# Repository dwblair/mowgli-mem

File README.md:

#mowgli-mem

https://github.com/adafruit/DS1307-breakout-board

https://tronixlabs.com.au/components/ics/real-time/microchip-rtc-mcp7940n-i-p-ds1307-equivalent/

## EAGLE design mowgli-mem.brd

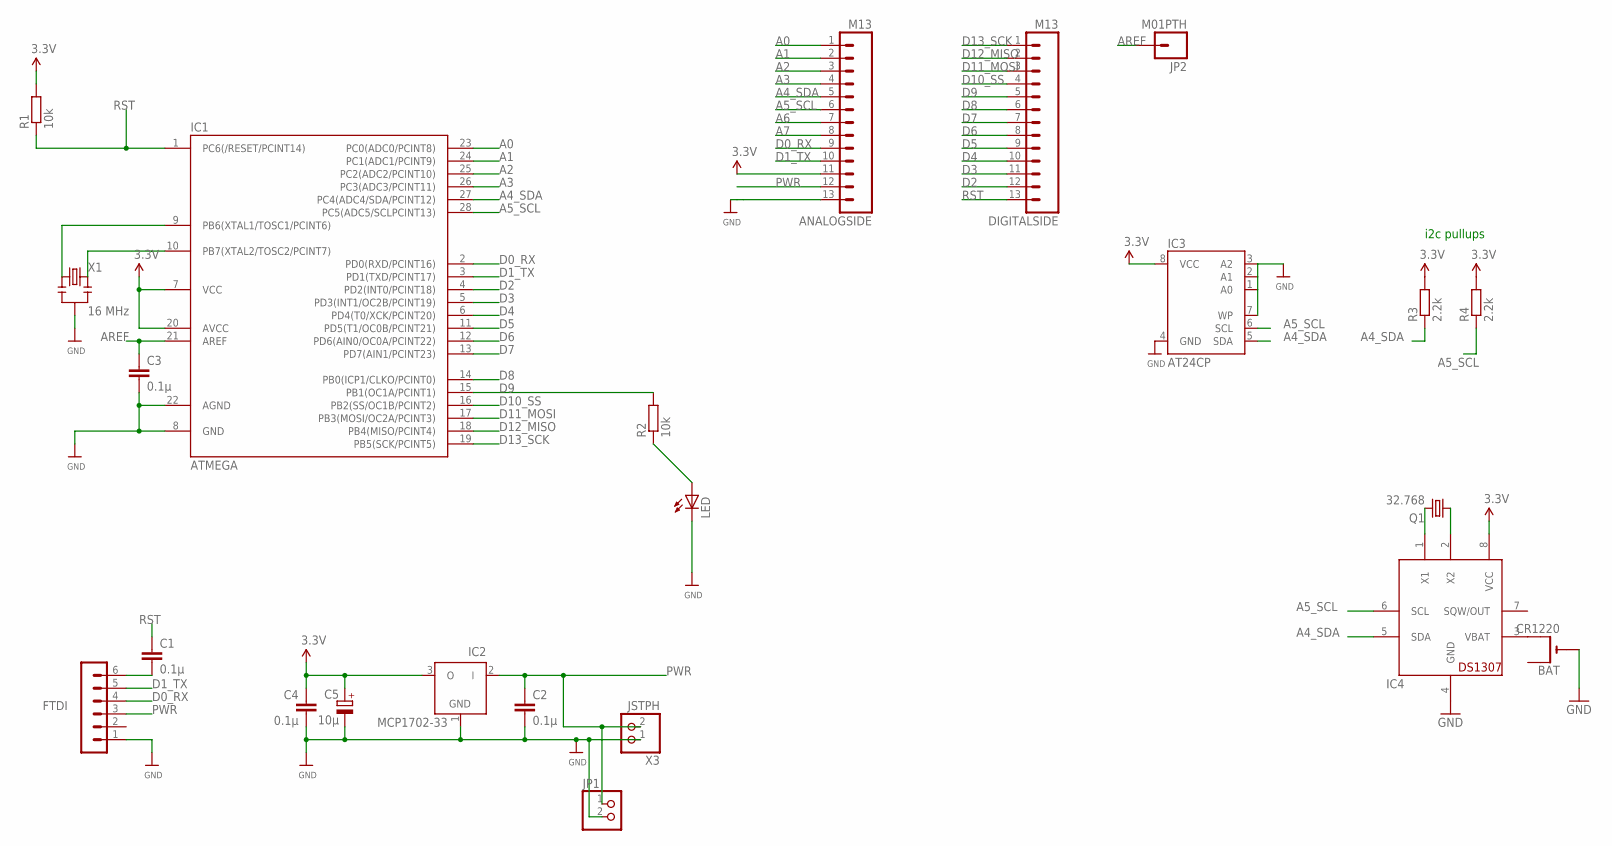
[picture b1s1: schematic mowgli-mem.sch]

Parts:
ANALOGSIDE: M13; 1X13
BAT: CR1220; CR1220-THM
C1, C2, C3, C4: 0.1µ; C025-024X044
C5: 10µ; E1,8-4
DIGITALSIDE: M13; 1X13
FTDI: FTDI; MA06-1
IC1: ATMEGA; DIL28-3
IC2: MCP1702-33; TO92
IC3: AT24CP; DIL08
IC4: DS1307; DIL08
JP1: PINHD-1X2; 1X02
JP2: M01PTH; 1X01
LED: LED3MM
Q1: 32.768; TC38H
R1, R2: 10k; 0204/7
R3, R4: 2.2k; 0204/7
X1: 16 MHz; RESONATOR-PTH
X3: JSTPH; JSTPH2

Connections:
A0: ANALOGSIDE.1, IC1.23 (PC0(ADC0/PCINT8))
A1: ANALOGSIDE.2, IC1.24 (PC1(ADC1/PCINT9))
A2: ANALOGSIDE.3, IC1.25 (PC2(ADC2/PCINT10))
A3: ANALOGSIDE.4, IC1.26 (PC3(ADC3/PCINT11))
A4_SDA: ANALOGSIDE.5, IC1.27 (PC4(ADC4/SDA/PCINT12)), IC3.5 (SDA), IC4.5 (SDA), R3.1
A5_SCL: ANALOGSIDE.6, IC1.28 (PC5(ADC5/SCLPCINT13)), IC3.6 (SCL), IC4.6 (SCL), R4.1
A6: ANALOGSIDE.7
A7: ANALOGSIDE.8
AREF: C3.1, IC1.21 (AREF), JP2.1
D0_RX: ANALOGSIDE.9, FTDI.4, IC1.2 (PD0(RXD/PCINT16))
D1_TX: ANALOGSIDE.10, FTDI.5, IC1.3 (PD1(TXD/PCINT17))
D2: DIGITALSIDE.12, IC1.4 (PD2(INT0/PCINT18))
D3: DIGITALSIDE.11, IC1.5 (PD3(INT1/OC2B/PCINT19))
D4: DIGITALSIDE.10, IC1.6 (PD4(T0/XCK/PCINT20))
D5: DIGITALSIDE.9, IC1.11 (PD5(T1/OC0B/PCINT21))
D6: DIGITALSIDE.8, IC1.12 (PD6(AIN0/OC0A/PCINT22))
D7: DIGITALSIDE.7, IC1.13 (PD7(AIN1/PCINT23))
D8: DIGITALSIDE.6, IC1.14 (PB0(ICP1/CLKO/PCINT0))
D9: DIGITALSIDE.5, IC1.15 (PB1(OC1A/PCINT1)), R2.2
D10_SS: DIGITALSIDE.4, IC1.16 (PB2(SS/OC1B/PCINT2))
D11_MOSI: DIGITALSIDE.3, IC1.17 (PB3(MOSI/OC2A/PCINT3))
D12_MISO: DIGITALSIDE.2, IC1.18 (PB4(MISO/PCINT4))
D13_SCK: DIGITALSIDE.1, IC1.19 (PB5(SCK/PCINT5))
GND: ANALOGSIDE.13, BAT.-, C2.2, C3.2, C4.2, C5.-, FTDI.1, IC1.8 (GND), IC1.22 (AGND), IC2.1 (GND), IC3.1 (A0), IC3.2 (A1), IC3.3 (A2), IC3.4 (GND), IC3.7 (WP), IC4.4 (GND), JP1.2, LED.K (C), X1.2, X3.1
unnamed: IC1.9 (PB6(XTAL1/TOSC1/PCINT6)), X1.1
unnamed: LED.A, R2.1
unnamed: IC4.1 (X1), Q1.2
unnamed: IC4.2 (X2), Q1.1
unnamed: C1.2, FTDI.6
unnamed: IC1.10 (PB7(XTAL2/TOSC2/PCINT7)), X1.3
unnamed: BAT.+2 (+1), IC4.3 (VBAT)
PWR: ANALOGSIDE.12, C2.1, FTDI.3, IC2.2 (I), JP1.1, X3.2
RST: C1.1, DIGITALSIDE.13, IC1.1 (PC6(/RESET/PCINT14)), R1.1
VCC: ANALOGSIDE.11, C4.1, C5.+, IC1.7 (VCC), IC1.20 (AVCC), IC2.3 (O), IC3.8 (VCC), IC4.8 (VCC), R1.2, R3.2, R4.2

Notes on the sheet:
i2c pullups

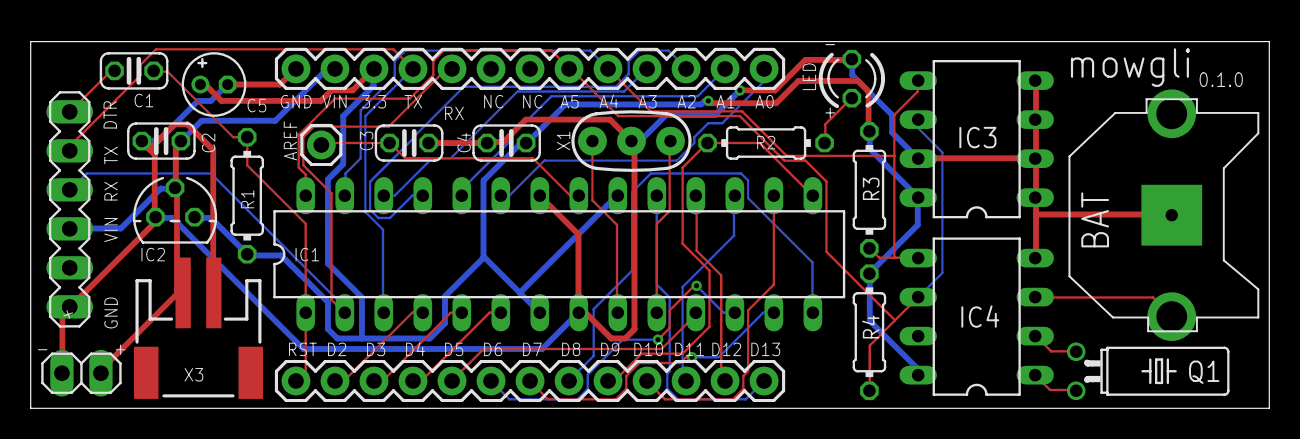
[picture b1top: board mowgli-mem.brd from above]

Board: 2 copper layers, 80.6 x 24.6 mm, 23 parts (0 on the bottom side), 32 nets.

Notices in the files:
parts and their libraries:
SparkFun-Connectors: Licensing: CC v3.0 Share-Alike You are welcome to use this library for commercial purposes.
microbuilder: This work is placed in the public domain, and may be freely used for commercial and non-commercial work with the following conditions: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
